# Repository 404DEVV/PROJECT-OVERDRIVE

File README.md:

# PROJECT-OVERDRIVE

PROJECT-OVERDRIVE is a DIY HP headphone amplifier project featuring:  

- **Microcontroller:** CH32V307  
- **DAC:** PCM5102A  
- **Headphone Amplifier:** MAX4410  
- **Display:** SSD1306 OLED for status and info  

## Status

- Schematic   

## License

This project is licensed under the **GNU General Public License v3.0 (GPL-3.0)**.  
You are free to use, modify, and distribute this project, but **any distributed derivative must also be open source under the same license**.

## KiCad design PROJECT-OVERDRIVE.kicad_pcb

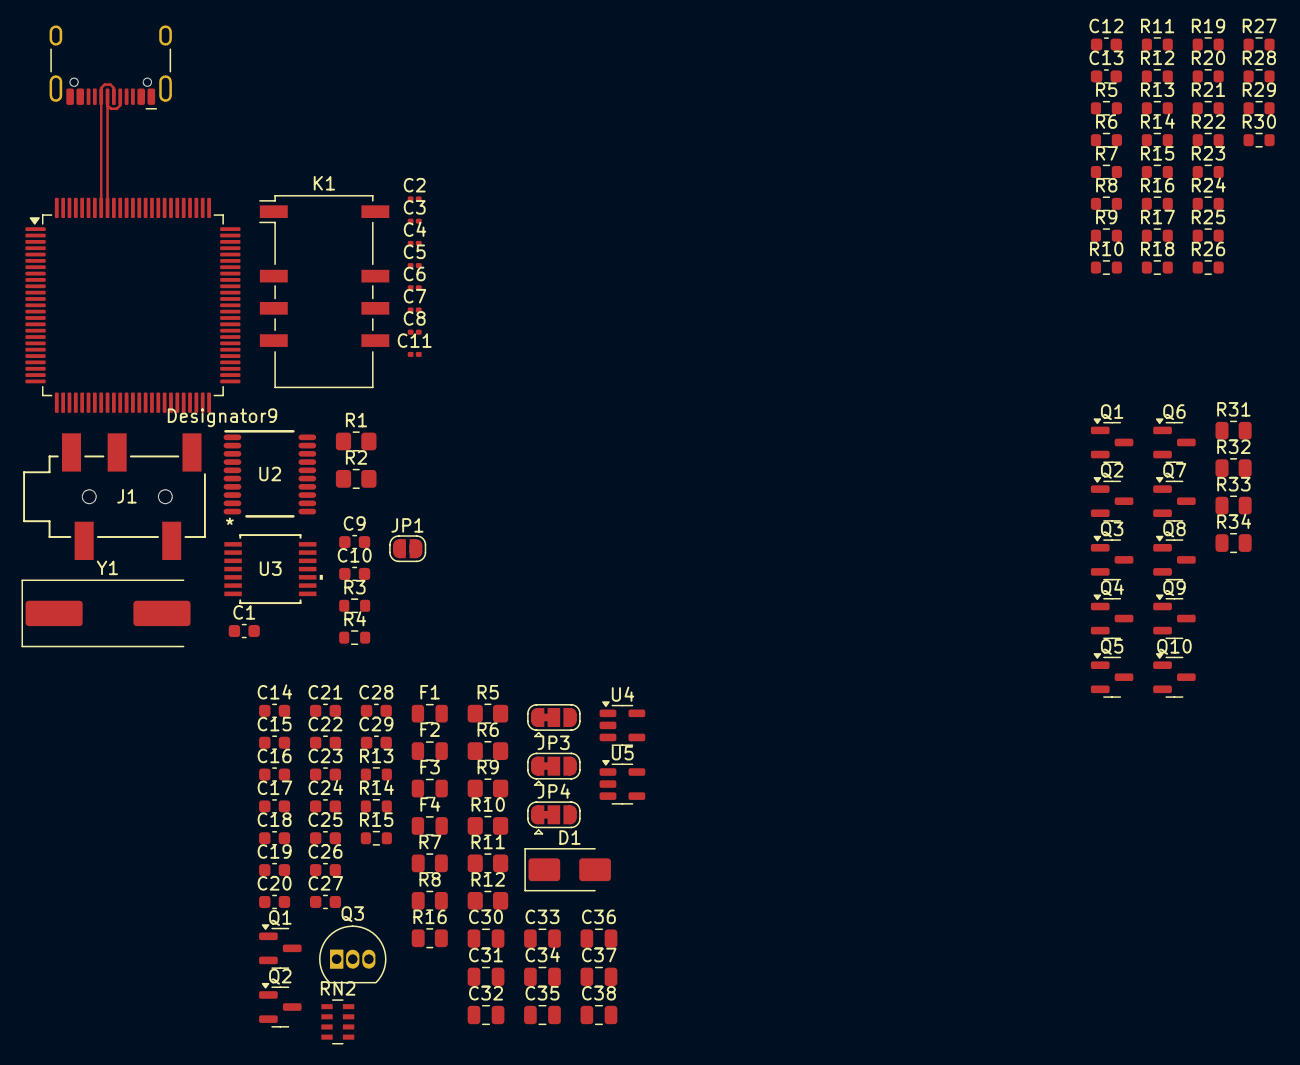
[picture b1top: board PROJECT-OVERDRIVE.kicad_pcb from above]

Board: 2 copper layers, 116 parts (0 on the bottom side), 66 nets.

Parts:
C1, C22: 2.2u; C_0603_1608Metric
C2, C3, C4, C5, C6, C7, C8, C11: 0.1u; C_0201_0603Metric
C9, C10: 18p; C_0603_1608Metric
C12, C13: 6n8; C_0603_1608Metric
C14, C15: 1u; C_0603_1608Metric
C16, C17, C18, C21, C26, C27: 0.1u; C_0603_1608Metric
C19, C20, C23, C24, C25, C28, C29: 4.7u; C_0603_1608Metric
C30, C31, C34, C36, C37: 4.7u; C_0805_2012Metric
C32, C33, C35, C38: 0.1u; C_0805_2012Metric
D1: SS34; D_SMA
F1: 200ma; Fuse_0805_2012Metric
F2: 100ma; Fuse_0805_2012Metric
F3, F4: 250ma; Fuse_0805_2012Metric
J1: PJ-327A0-SMT; CONN5_PJ-327A0_XKB
J2: USB_C_Receptacle_USB2.0_16P; USB_C_Receptacle_HCTL_HC-TYPE-C-16P-01A
JP1: Jumper_2_Open; SolderJumper-2_P1.3mm_Open_RoundedPad1.0x1.5mm
JP2, JP3, JP4: SolderJumper_3_Bridged12; SolderJumper-3_P1.3mm_Bridged12_RoundedPad1.0x1.5mm
K1: G6S-2; Relay_DPDT_Omron_G6S-2F
Q1, Q2#2: AO3401A; SOT-23
Q1#2, Q2, Q3#2, Q4, Q5, Q6, Q7, Q8, Q9, Q10: AO3400A; SOT-23
Q3: S8050; TO-92_Inline
R1, R2: 220; R_0805_2012Metric_Pad1.20x1.40mm_HandSolder
R3, R4: 5k1; R_0603_1608Metric
R5, R6: 22k; R_0805_2012Metric_Pad1.20x1.40mm_HandSolder
R5#2, R6#2, R7, R8, R9, R10, R11#2, R12#2, R13#2, R14#2: 1k; R_0603_1608Metric
R7#2, R31, R32, R33, R34: 10k; R_0805_2012Metric
R8#2: 100k; R_0805_2012Metric
R9#2, R10#2: 1k; R_0805_2012Metric_Pad1.20x1.40mm_HandSolder
R11, R12: 10k; R_0805_2012Metric_Pad1.20x1.40mm_HandSolder
R13, R14, R15#2: 22r; R_0603_1608Metric
R15, R16#2, R17, R18, R19, R20, R21, R22, R23, R24, R25, R26, R27, R28, R29, R30: 68; R_0603_1608Metric
R16: 1k; R_0805_2012Metric
RN2: 22; R_Array_Concave_4x0603
U1: CH32V30xVxTx; LQFP-100_14x14mm_P0.5mm
U2: PCM5102APWR; PW0020A_N
U3: MAX4410EUD+; 21-0066J_14_MXM
U4, U5: AP2112K-3.3; SOT-23-5
Y1: 8M; Crystal_SMD_HC49-SD

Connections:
+3.3VA: C25.1, C26.1, C27.1, Q2#2.3 (D), U3.2 (PVDD), U3.9 (SVDD)
+3.3VDAC: C16.2, C17.2, Q1.3 (D), U2.1 (CPVDD), U2.8 (AVDD)
+5V: C33.1, C34.1, C35.1, F3.2, K1.1, U4.1 (VIN), U5.1 (VIN)
AMP_MUTE: U3.1 (*SHDNL), U3.12 (*SHDNR)
DAC_BCK: RN2.6 (R3.2), U2.13 (BCK)
DAC_DIN: RN2.8 (R1.2), U2.14 (DIN)
DAC_LRCLK: RN2.5 (R4.2), U2.15 (LRCK)
DAC_MUTE: RN2.7 (R2.2), U2.17 (XSMT)
GND: C2.2, C3.2, C4.2, C5.2, C6.2, C7.2, C8.1, C9.2, C10.2, C11.2, C12.2, C13.2, C19.1, C20.1, C21.1, C23.2, C24.2, C25.2, C26.2, C27.2, C30.2, C31.2, C32.2, C33.2, C34.2, C35.2, C36.2, C37.2, C38.2, J1.3, J1.4, J2.A1 (GND), J2.A12 (GND), J2.B1 (GND), J2.B12 (GND), J2.S1 (SHIELD), JP2.1 (A), JP3.1 (A), JP4.1 (A), Q1#2.2 (S), Q2.2 (S), Q3.1 (E), Q3#2.2 (S), Q4.2 (S), Q5.2 (S), Q6.2 (S), Q7.2 (S), Q8.2 (S), Q9.2 (S), Q10.2 (S), R3.1, R4.1, R5.2, R6.2, R8#2.2, U1.10 (VSS), U1.19 (VSSA), U1.20 (VREF-), U1.27 (VSS), U1.49 (VSS), U1.74 (VSS), U1.99 (VSS), U2.3 (CPGND), U2.9 (AGND), U2.12 (SCK), U2.19 (DGND), U3.4 (PGND), U3.14 (SGND), U4.2 (GND), U5.2 (GND)
unnamed: C12.1, K1.5, R2.2, R31.2
unnamed: C13.1, K1.8, R1.2, R32.2
unnamed: C16.1, C17.1, C18.1
unnamed: D1.1 (K), F3.1, F4.2, Q1#2.3 (D)
unnamed: J1.2, K1.9, R5.1
unnamed: J1.5, K1.4, R6.1
unnamed: J2.A5 (CC1), R3.2
unnamed: J2.B5 (CC2), R4.2
unnamed: JP1.2 (B), U1.94 (BOOT0)
unnamed: JP2.2 (C), U2.16 (FMT)
unnamed: JP3.2 (C), U2.10 (DEMP)
unnamed: JP4.2 (C), U2.11 (FLT)
unnamed: C28.2, C29.2
unnamed: Q1.1 (G), Q1#2.1 (G), R5#2.1, R9#2.2, R12.1
unnamed: Q2.1 (G), Q2#2.1 (G), R6#2.1, R10#2.2, R11.1
unnamed: Q3.2 (B), R16.2
unnamed: K1.12, Q3.3 (C)
unnamed: Q3#2.1 (G), R7.1
unnamed: Q4.1 (G), R8.1
unnamed: Q5.1 (G), R9.1
unnamed: Q6.1 (G), R10.1
unnamed: Q7.1 (G), R11#2.1
unnamed: Q8.1 (G), R12#2.1
unnamed: Q9.1 (G), R13#2.1
unnamed: Q10.1 (G), R14#2.1
unnamed: RN2.1 (R1.1), U1.54 (PB15)
unnamed: RN2.2 (R2.1), U1.53 (PB14)
unnamed: RN2.3 (R3.1), U1.52 (PB13)
unnamed: RN2.4 (R4.1), U1.51 (PB12)
unnamed: C9.1, U1.12 (OSC_IN), Y1.2
unnamed: C10.1, U1.13 (OSC_OUT), Y1.1
unnamed: R13.2, U1.77 (PA15)
unnamed: R14.2, U1.89 (PB3)
unnamed: R15#2.2, U1.91 (PB5)
unnamed: J2.A7 (D-), J2.B7 (D-), U1.92 (PB6)
unnamed: J2.A6 (D+), J2.B6 (D+), U1.93 (PB7)
unnamed: C8.2, U1.14 (~RST)
unnamed: C22.2, U2.4 (CAPM)
unnamed: C22.1, U2.2 (CAPP)
unnamed: C19.2, C20.2, C21.2, U2.18 (LDOO)
unnamed: R1.1, U2.6 (OUTL)
unnamed: R2.1, U2.7 (OUTR)
unnamed: C23.1, U2.5 (VNEG)
unnamed: C1.2, U3.5 (C1N)
unnamed: C1.1, U3.3 (C1P)
unnamed: R32.1, R34.1, U3.10 (INL)
unnamed: R31.1, R33.1, U3.13 (INR)
unnamed: K1.10, R34.2, U3.8 (OUTL)
unnamed: K1.3, R33.2, U3.11 (OUTR)
unnamed: C24.1, U3.6 (PVSS), U3.7 (SVSS)
unnamed: C30.1, C31.1, C32.1, F2.1, U4.5 (VOUT)
unnamed: C36.1, C37.1, C38.1, F1.1, U5.5 (VOUT)
unnamed: R7#2.2, R8#2.1
VBUS: D1.2 (A), J2.A4 (VBUS), J2.A9 (VBUS), J2.B4 (VBUS), J2.B9 (VBUS)
VDD: C2.1, C3.1, C4.1, C5.1, C6.1, C7.1, C11.1, F1.2, JP1.1 (A), R7#2.1, U1.11 (VDD), U1.21 (VREF+), U1.22 (VDDA), U1.28 (VDD), U1.50 (VIO), U1.75 (VDD), U1.100 (VIO)
VDDA: F2.2, Q1.2 (S), Q2#2.2 (S), R11.2, R12.2
VDDF: C18.2, JP2.3 (B), JP3.3 (B), JP4.3 (B), U2.20 (DVDD)

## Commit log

2025-08-23 Auto-save: 2025-08-23 21:01:08
2025-08-23 Auto-save: 2025-08-23 21:01:10
2025-08-23 Auto-save: 2025-08-23 21:01:15
2025-08-23 Auto-save: 2025-08-23 21:01:34
2025-08-23 very ambitious work:added the vdda flag on the ap2112k for analog
2025-08-23 Create README.md
    simple readme(to be changed later)
2025-08-23 Create LICENSE
2025-08-23 Update README.md with license info
2025-08-23 Add fuses
2025-08-23 finished power supply section
2025-08-23 added exp port(to be finished)
2025-08-24 expansion port mostly finished(TODO:Add some gpios to there) relay circuit finished(need to connect to mcu)
2025-09-09 idkmyinternetwasdead.git
2025-09-17 changed readme ig
2025-09-19 fixed up op amp connection
2025-10-12 Add some connections to the mcu
2025-10-18 wired up the led bus on the mcu side, started spi(flash and oled) wiring
2025-10-23 spi connections finished
